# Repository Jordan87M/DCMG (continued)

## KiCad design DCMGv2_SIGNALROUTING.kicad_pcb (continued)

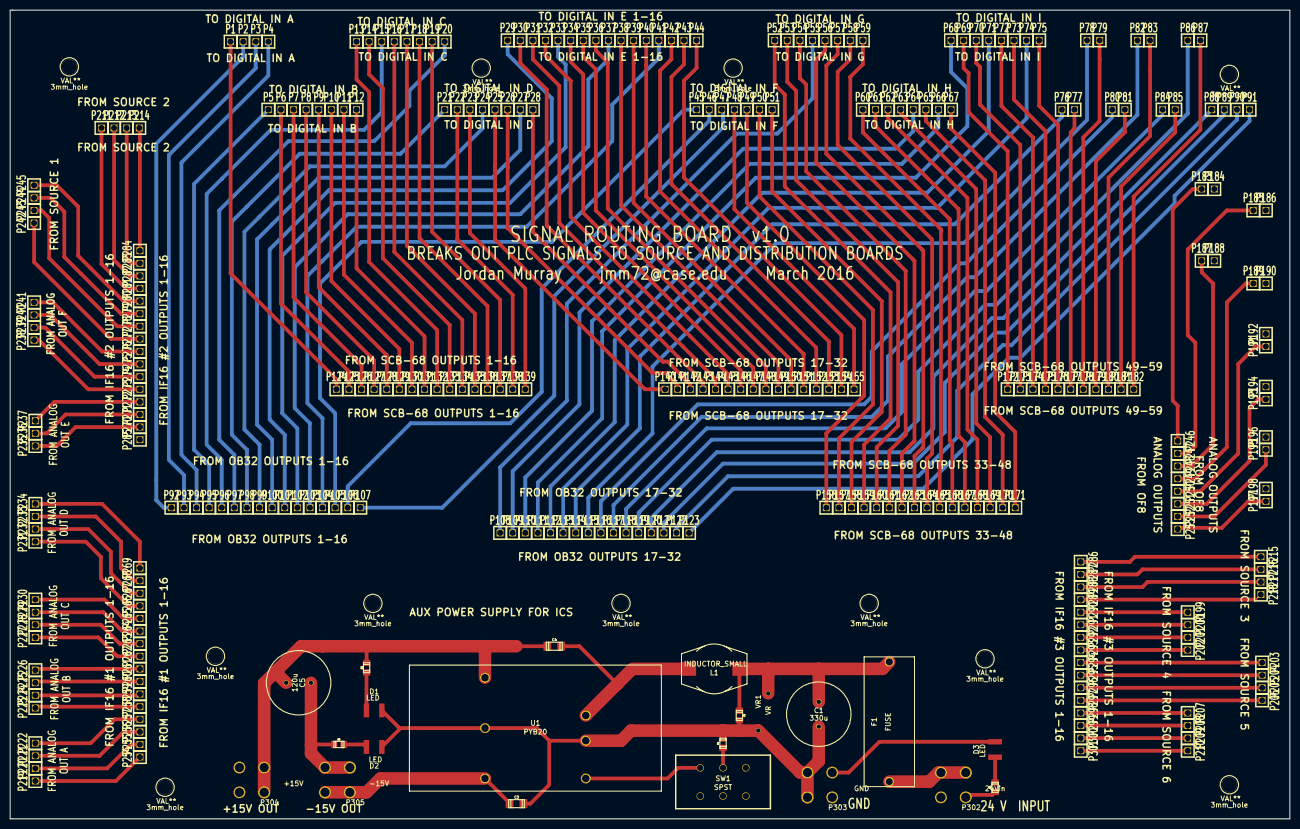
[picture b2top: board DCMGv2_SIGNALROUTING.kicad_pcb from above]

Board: 2 copper layers, 258.1 x 163.1 mm, 333 parts (0 on the bottom side), 157 nets.

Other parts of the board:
3mm_hole, 3mm_hole#2, 3mm_hole#3, 3mm_hole#4, 3mm_hole#5, 3mm_hole#6, 3mm_hole#7, 3mm_hole#8, 3mm_hole#9, 3mm_hole#10, 3mm_hole#11: VAL**; 3mm_hole

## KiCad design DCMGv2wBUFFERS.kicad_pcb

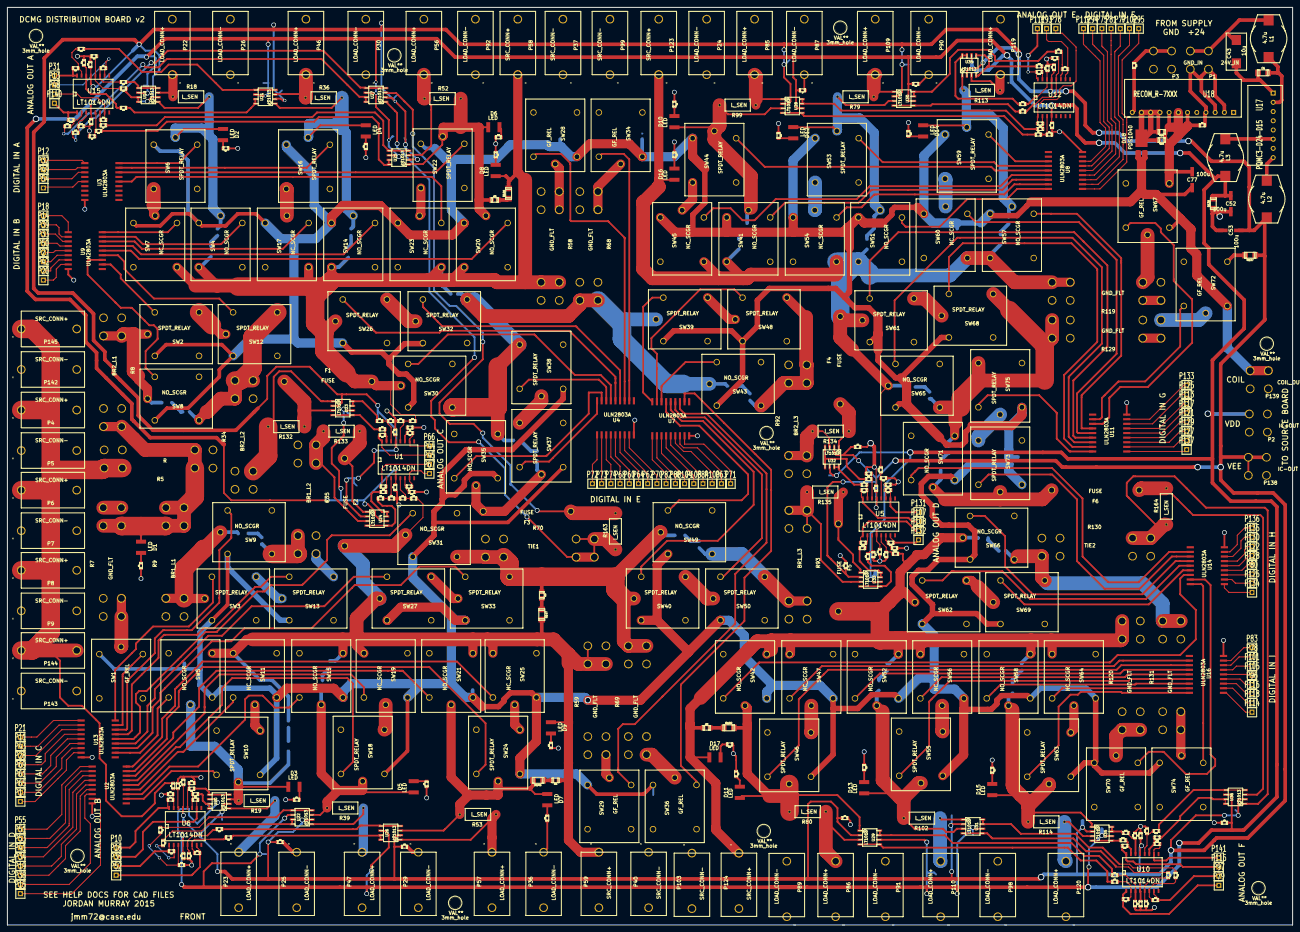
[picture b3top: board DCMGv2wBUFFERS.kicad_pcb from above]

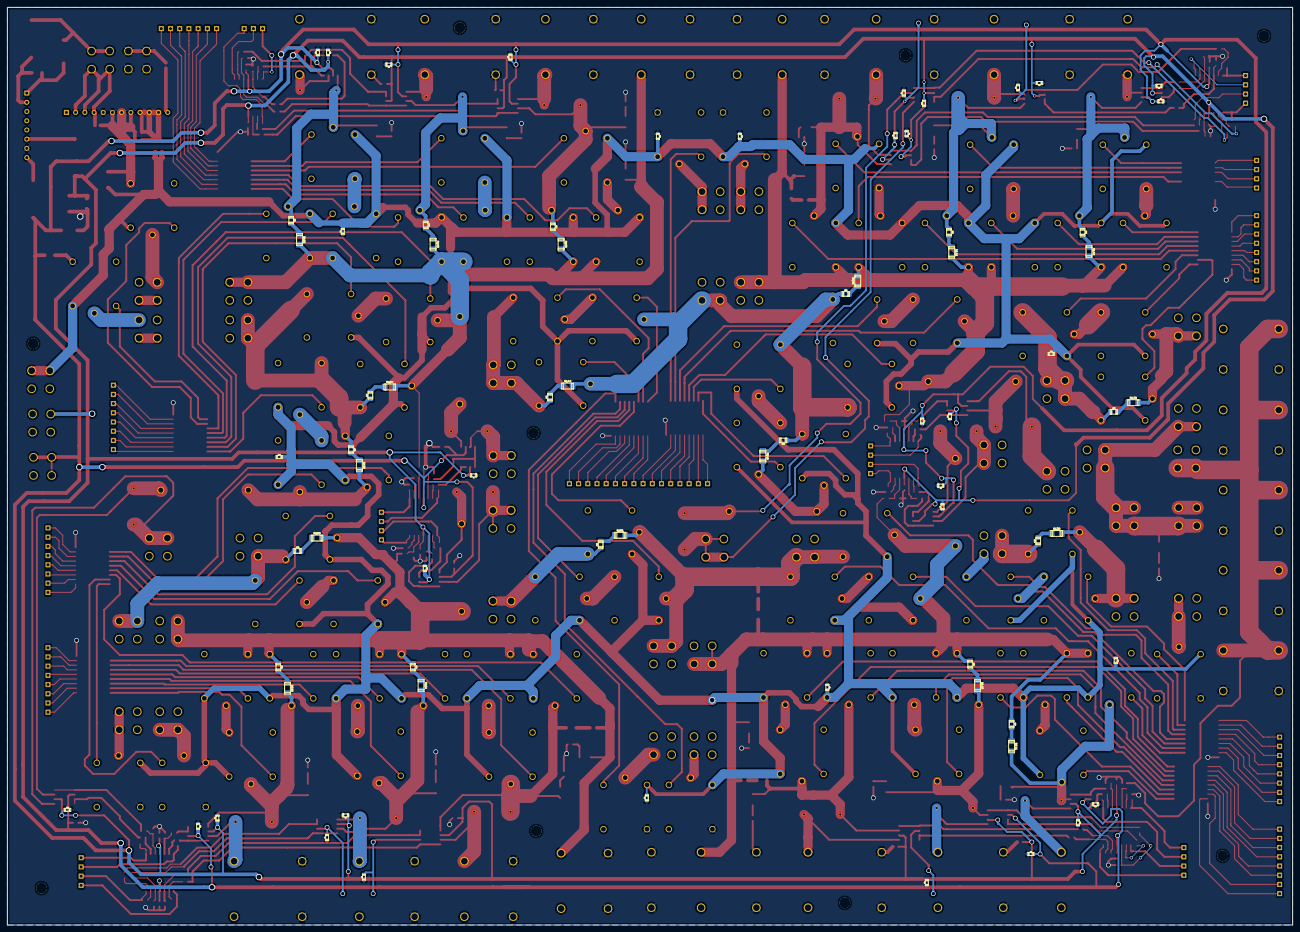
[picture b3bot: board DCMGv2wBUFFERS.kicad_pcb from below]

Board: 2 copper layers, 354.3 x 253.0 mm, 548 parts (72 on the bottom side), 389 nets.

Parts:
3mm_hole, 3mm_hole#2, 3mm_hole#3, 3mm_hole#4, 3mm_hole#5, 3mm_hole#6, 3mm_hole#7, 3mm_hole#8, 3mm_hole#9: VAL**; 3mm_hole
C1: 1u; c_1206
C2, C3, C4, C5, C6, C7, C8, C9, C10, C11, C12, C13, C14, C15, C16, C17, C18, C19, C20, C21, C22, C23, C24, C25, C26, C27, C28, C29, C30, C31, C32, C33, C34, C35, C36, C37, C38, C39, C40, C41, C42, C78, C79, C80, C81, C82, C83, C84: VCC_BYP; c_0603
C43: 10u; c_2917
C44, C45, C46, C47, C48, C49, C50, C51: COIL_BYPASS; c_0603
C52, C53, C77: 100u; PANASONIC_CAP_D8
C54, C55, C56, C57, C58, C59, C60, C61, C62, C63, C64, C65, C66, C67, C68, C69, C70, C71, C72, C73, C74, C75: C_SNUB; c_0805
C76: 1u; c_0603
D1, D2, D3, D4, D5, D6, D7, D8, D9, D10, D11, D12, D13, D14, D15, D16, D17: LED; 1209
D18: PDS1040; POWERDI5
F1, F2, F3, F4, F5, F6: FUSE; OMNI-BLOCK
L1, L2, L3: 4.7u; SDR1005
P1: 24V_IN; Screw Terminal 8191
P2: IC+OUT; Screw Terminal 8191
P3: GND_IN; Screw Terminal 8191
P4, P6, P8, P58, P59, P123, P124, P144, P145: SRC_CONN+; DELTRON BANANA
P5, P7, P9, P37, P40, P99, P103, P142, P143: SRC_CONN-; DELTRON BANANA
P10, P66, P67, P131, P132: BUS_V_SIG; SIL-1
P11, P62, P63, P70, P71, P125, P126, P133, P134: GF_SIG; SIL-1
P12, P15, P20, P21, P32, P34, P49, P51, P60, P61, P72, P75, P78, P82, P84, P94, P96, P112, P114, P121, P122, P135: CTRL_SIG; SIL-1
P13, P16, P31, P35, P44, P45, P48, P52, P76, P79, P93, P97, P107, P108, P111, P115, P140, P141: LOAD_I_SIG; SIL-1
P14, P17, P33, P38, P42, P43, P50, P53, P68, P69, P73, P77, P80, P95, P101, P104, P106, P113, P116, P129, P130, P136: NO_SCGR_SIG; SIL-1
P18, P19, P27, P28, P39, P41, P54, P55, P64, P65, P74, P81, P83, P88, P100, P102, P105, P117, P118, P127, P128, P137: NC_SCGR_SIG; SIL-1
P22, P23, P46, P47, P56, P57, P85, P86, P109, P110, P119, P120: LOAD_CONN+; DELTRON BANANA
P24, P25, P26, P29, P30, P36, P87, P89, P90, P91, P92, P98: LOAD_CONN-; DELTRON BANANA
P138: IC-OUT; Screw Terminal 8191
P139: COIL_OUT; Screw Terminal 8191
R1, R61, R63, R122, R124: VS_R2; c_0603
R2, R60, R64, R121, R125: VS_R4; c_0603
R3, R62, R65, R123, R126: VS_R1; c_0603
R4, R66, R67, R127, R128: VS_R3; c_0603
R5: R; Double Terminal 8191
R6, R20, R21, R42, R43, R54, R55, R81, R82, R103, R104, R115, R116: CLIM; c_0603
R7, R58, R59, R68, R69, R119, R120, R129, R131: GND_FLT; Double Terminal 8191
R8: BR2_L1; Double Terminal 8191
R9: BR1_L1; Double Terminal 8191
R10, R11, R22, R23, R44, R45, R71, R72, R83, R84, R105, R106, R168, R172: IS_R3; c_0603
R12, R17, R24, R31, R46, R51, R73, R78, R89, R96, R107, R112, R167, R171: IS_R1; c_0603
R13, R16, R25, R30, R47, R50, R74, R77, R90, R95, R108, R111, R166, R170: IS_R4; c_0603
R14, R15, R26, R29, R48, R49, R75, R76, R91, R94, R109, R110, R165, R169: IS_R2; c_0603
R18, R19, R36, R39, R52, R53, R79, R80, R99, R102, R113, R114: L_SEN; OHMITE_1W
R27, R28, R32, R33, R37, R38, R40, R41, R85, R86, R87, R88, R97, R98, R100, R101, R160: R; c_0603
R34: BR2_L2; Double Terminal 8191
R35: BR1_L2; Double Terminal 8191
R56, R57, R117, R118: C_LIM; c_0603
R70: TIE1; Double Terminal 8191
R92: BR2_L3; Double Terminal 8191
R93: BR1_L3; Double Terminal 8191
R130: TIE2; Double Terminal 8191
R132, R133, R134, R135, R163, R164: I_SEN; OHMITE_1W
R136, R137: MINLOAD_S; c_1206
R138, R139, R140, R141, R142, R143, R144, R145, R146, R147, R148, R149, R150, R151, R152, R153, R154, R155, R156, R157, R158, R159: R_SNUB; c_1206
R161, R162: 1k; c_0805
SW1, SW28, SW29, SW34, SW36, SW67, SW70, SW72, SW74: GF_REL; TECONN_ORWH
SW2, SW3, SW6, SW10, SW12, SW13, SW16, SW18, SW22, SW24, SW26, SW27, SW32, SW33, SW37, SW38, SW39, SW40, SW44, SW46, SW48, SW50, SW53, SW55, SW59, SW61, SW62, SW63, SW68, SW69, SW73, SW75: SPDT_RELAY; TECONN_ORWH
SW4, SW5, SW8, SW9, SW14, SW15, SW20, SW21, SW30, SW31, SW35, SW41, SW42, SW43, SW49, SW51, SW52, SW57, SW58, SW65, SW66, SW71: NO_SCGR; TECONN_ORWH
SW7, SW11, SW17, SW19, SW23, SW25, SW45, SW47, SW54, SW56, SW60, SW64: NC_SCGR; TECONN_ORWH
U1, U5, U6, U10, U12, U15: LT1014DN; SO16W
U2, U3, U4, U7, U8, U9, U11, U13, U14, U16: ULN2803A; SOIC-18
U17: PQMC3-D24-D15; SIL-8 PQMC
U18: RECOM_R-7XXX; R-7xxx_SIL-12
U19, U20, U21, U22, U23, U24, U25, U26, U27, U28, U29, U30, U31, U32, U33, U34, U35, U36: LT1013; so-8

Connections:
COIL_POW+: C44.1, C45.1, C46.1, C47.1, C48.1, C49.1, C50.1, C51.1, C77.1, D18.2, P139.1, SW1.2, SW2.2, SW3.2, SW4.2, SW5.2, SW6.2, SW7.2, SW8.2, SW9.2, SW10.2, SW11.2, SW12.2, SW13.2, SW14.2, SW15.2, SW16.2, SW17.2, SW18.2, SW19.2, SW20.2, SW21.2, SW22.2, SW23.2, SW24.2, SW25.2, SW26.2, SW27.2, SW28.2, SW29.2, SW30.2, SW31.2, SW32.2, SW33.2, SW34.2, SW35.2, SW36.2, SW37.2, SW38.2, SW39.2, SW40.2, SW41.2, SW42.2, SW43.2, SW44.2, SW45.2, SW46.2, SW47.2, SW48.2, SW49.2, SW50.2, SW51.2, SW52.2, SW53.2, SW54.2, SW55.2, SW56.2, SW57.2, SW58.2, SW59.2, SW60.2, SW61.2, SW62.2, SW63.2, SW64.2, SW65.2, SW66.2, SW67.2, SW68.2, SW69.2, SW70.2, SW71.2, SW72.2, SW73.2, SW74.2, SW75.2
GND: C1.2, C2.2, C3.2, C4.2, C5.2, C6.2, C7.2, C8.2, C9.2, C10.1, C11.1, C12.1, C13.1, C14.1, C15.1, C16.2, C17.1, C18.1, C19.1, C20.2, C21.1, C22.1, C23.2, C24.2, C25.2, C26.2, C27.2, C28.2, C29.2, C30.2, C31.1, C32.1, C33.1, C34.1, C35.1, C36.1, C37.1, C38.1, C39.2, C40.1, C41.2, C42.1, C43.2, C44.2, C45.2, C46.2, C47.2, C48.2, C49.2, C50.2, C51.2, C52.2, C53.1, C76.2, C77.2, C78.2, C79.1, C80.2, C81.1, C82.2, C83.2, C84.1, P3.1, P5.1, P7.1, P9.1, P24.1, P25.1, P26.1, P29.1, P30.1, P36.1, P37.1, P40.1, P87.1, P89.1, P90.1, P91.1, P92.1, P98.1, P99.1, P103.1, P142.1, P143.1, R2.2, R3.2, R6.2, R13.1, R16.1, R20.2, R21.2, R25.1, R30.1, R32.1, R33.1, R42.2, R43.2, R47.1, R50.1, R54.2, R55.2, R56.2, R57.2, R60.2, R62.2, R64.2, R65.2, R74.1, R77.1, R81.2, R82.2, R87.1, R88.1, R90.1, R95.1, R103.2, R104.2, R108.1, R111.1, R115.2, R116.2, R117.2, R118.2, R121.2, R123.2, R125.2, R126.2, R136.2, R137.1, R160.2, R161.2, R162.2, R166.1, R170.1, SW1.10, SW28.10, SW29.10, SW34.10, SW36.10, SW67.10, SW70.10, SW72.10, SW74.10, U2.9, U3.9, U4.9, U7.9, U8.9, U9.9, U11.9, U13.9, U14.9, U16.9, U17.1, U17.7, U18.5, U18.6, U18.7, U18.8
IC_POW+: C2.1, C3.1, C4.1, C5.1, C6.1, C7.1, C8.1, C9.1, C16.1, C20.1, C23.1, C24.1, C25.1, C26.1, C27.1, C28.1, C29.1, C30.1, C39.1, C41.1, C52.1, C78.1, C80.1, C82.1, C83.1, L3.2, P2.1, R136.1, U1.4, U5.4, U6.4, U10.4, U12.4, U15.4, U19.6, U20.6, U21.6, U22.6, U23.6, U24.6, U25.6, U26.6, U27.6, U28.6, U29.6, U30.6, U31.6, U32.6, U33.6, U34.6, U35.6, U36.6
IC_POW-: C10.2, C11.2, C12.2, C13.2, C14.2, C15.2, C17.2, C18.2, C19.2, C21.2, C22.2, C31.2, C32.2, C33.2, C34.2, C35.2, C36.2, C37.2, C38.2, C40.2, C42.2, C53.2, C79.2, C81.2, C84.2, L2.2, P138.1, R137.2, U1.13, U5.13, U6.13, U10.13, U12.13, U15.13, U19.2, U20.2, U21.2, U22.2, U23.2, U24.2, U25.2, U26.2, U27.2, U28.2, U29.2, U30.2, U31.2, U32.2, U33.2, U34.2, U35.2, U36.2
unnamed: P56.1, R52.2, U25.3
unnamed: P46.1, R36.2, U21.3
unnamed: P48.1, R44.1, U15.7
unnamed: SW60.9, U11.14
unnamed: SW57.9, U11.13
unnamed: P117.1, U11.5
unnamed: SW59.9, U8.12
unnamed: SW59.10, SW60.5
unnamed: R44.2, R46.1, U15.6
unnamed: P113.1, U11.6
unnamed: P112.1, U8.7
unnamed: P125.1, U11.7
unnamed: P66.1, R66.2, U1.10
unnamed: R13.2, R14.1, U15.12
unnamed: P22.1, R18.2, U19.3
unnamed: SW6.10, SW7.5
unnamed: R62.1, R66.1, U1.11
unnamed: R47.2, R48.1, U15.5
unnamed: P31.1, R22.1, U15.16
unnamed: R22.2, R24.1, U15.15
unnamed: R25.2, R26.1, U15.14
unnamed: P13.1, R10.1, U15.10
unnamed: R10.2, R12.1, U15.11
unnamed: R121.1, R122.2, U5.12
unnamed: R123.1, R127.1, U5.11
unnamed: P131.1, R127.2, U5.10
unnamed: SW44.10, SW45.5
unnamed: R119.2, SW67.5
unnamed: D10.2, R81.1
unnamed: D12.2, R103.1
unnamed: D14.2, R115.1
unnamed: P76.1, R71.1, U12.1
unnamed: R71.2, R73.1, U12.2
unnamed: R74.2, R75.1, U12.3
unnamed: SW53.9, U8.13
unnamed: SW53.10, SW54.5
unnamed: SW54.9, U8.17
unnamed: P102.1, U8.2
unnamed: SW51.9, U8.18
unnamed: P95.1, U8.1
unnamed: P94.1, U8.6
unnamed: D16.2, R117.1
unnamed: SW44.9, U8.14
unnamed: SW67.9, U11.12
unnamed: SW45.9, U8.15
unnamed: P81.1, U8.4
unnamed: SW41.9, U8.16
unnamed: P77.1, U8.3
unnamed: P75.1, U8.5
unnamed: P79.1, R72.1, U10.1
unnamed: R94.1, R95.2, U10.5
unnamed: R84.2, R96.1, U10.6
unnamed: P97.1, R84.1, U10.7
unnamed: R72.2, R78.1, U10.2
unnamed: P86.1, R80.2, U29.3
unnamed: R76.1, R77.2, U10.3
unnamed: P110.1, R102.2, U31.1
unnamed: P120.1, R114.2, U35.3
unnamed: P115.1, R106.1, U10.16
unnamed: R106.2, R112.1, U10.15
unnamed: R110.1, R111.2, U10.14
unnamed: D17.2, R118.1
unnamed: D15.2, R116.1
unnamed: D13.2, R104.1
unnamed: D11.2, R82.1
unnamed: SW46.9, U16.12
unnamed: SW70.9, U14.17
unnamed: SW47.9, U16.11
unnamed: P132.1, R128.2, U5.7
unnamed: D11.1, R80.1, R152.1, SW42.5, SW46.5, U29.1
unnamed: SW46.10, SW47.5
unnamed: R126.1, R128.1, U5.6
unnamed: R124.2, R125.1, U5.5
unnamed: R120.2, SW70.5
unnamed: SW28.9, U4.12
unnamed: SW6.9, U3.18
unnamed: P14.1, U9.2
unnamed: SW4.9, U9.17
unnamed: P18.1, U9.1
unnamed: SW7.9, U9.18
unnamed: P12.1, U3.1
unnamed: SW16.10, SW17.5
unnamed: D4.2, R42.1
unnamed: R60.1, R61.2, U1.12
unnamed: R58.2, SW28.5
unnamed: D2.2, R20.1
unnamed: D6.2, R54.1
unnamed: D8.2, R56.1
unnamed: P50.1, U9.5
unnamed: P62.1, U4.7
unnamed: P49.1, U3.3
unnamed: SW22.9, U3.16
unnamed: SW20.9, U9.14
unnamed: P54.1, U3.5
unnamed: SW23.9, U3.14
unnamed: SW16.9, U3.17
unnamed: SW17.9, U9.16
unnamed: P39.1, U9.3
unnamed: SW14.9, U9.15
unnamed: P33.1, U9.4
unnamed: P32.1, U3.2
unnamed: R90.2, R91.1, U12.12
unnamed: SW22.10, SW23.5
unnamed: R169.1, R170.2, U10.12
unnamed: R171.1, R172.2, U10.11
unnamed: P141.1, R172.1, U10.10
unnamed: C63.2, R69.1, R70.2, R151.1, SW31.10, SW33.1, SW40.5, SW49.5
unnamed: F3.1, R163.1, U27.3
unnamed: R70.1, R163.2, U27.1
unnamed: D3.1, R19.1, R141.1, SW5.5, SW10.5, U20.3
unnamed: R15.2, U20.4, U20.5
unnamed: P140.1, R168.1, U15.1
unnamed: R167.1, R168.2, U15.2
unnamed: R165.1, R166.2, U15.3
unnamed: R9.2, R138.1, SW3.5, SW9.5
unnamed: R160.1, U18.12
unnamed: D18.1, R161.1, R162.1, U18.9, U18.10, U18.11
unnamed: R46.2, U25.4, U25.5
unnamed: R48.2, U25.7, U25.8
unnamed: R165.2, U27.4, U27.5
unnamed: R112.2, U35.4, U35.5
unnamed: R110.2, U35.7, U35.8
unnamed: R12.2, U19.4, U19.5
unnamed: R26.2, U21.7, U21.8
unnamed: R24.2, U21.4, U21.5
unnamed: R167.2, U27.7, U27.8
unnamed: R49.2, U26.4, U26.5
unnamed: R31.2, U22.7, U22.8
unnamed: D7.1, R53.1, R145.1, SW21.5, SW24.5, U26.3
unnamed: P47.1, R39.2, U22.1
unnamed: P57.1, R53.2, U26.1
unnamed: R29.2, U22.4, U22.5
unnamed: D5.1, R39.1, R143.1, SW15.5, SW18.5, U22.3
unnamed: R17.2, U20.7, U20.8
unnamed: P23.1, R19.2, U20.1
unnamed: R78.2, U29.4, U29.5
unnamed: R96.2, U31.7, U31.8
unnamed: R94.2, U31.4, U31.5
unnamed: L3.1, U17.6
unnamed: R76.2, U29.7, U29.8
unnamed: R51.2, U26.7, U26.8
unnamed: C56.1, R139.2
unnamed: C62.1, R146.2
unnamed: C65.1, R149.2
unnamed: C73.1, R157.2
unnamed: C74.1, R158.2
unnamed: C59.1, R143.2
unnamed: C58.1, R142.2
unnamed: C72.1, R156.2
unnamed: C70.1, R154.2
unnamed: C67.1, R152.2
unnamed: C61.1, R145.2
unnamed: C57.1, R141.2
unnamed: C55.2, D2.1, R18.1, SW4.5, SW6.5, U19.1
unnamed: C55.1, R140.2
unnamed: C54.1, R138.2
unnamed: C63.1, R147.2
unnamed: C68.1, R151.2
unnamed: R105.2, R107.1, U12.15
unnamed: P111.1, R105.1, U12.16
unnamed: R108.2, R109.1, U12.14
unnamed: P93.1, R83.1, U12.10
unnamed: R83.2, R89.1, U12.11
unnamed: C58.2, D4.1, R36.1, SW14.5, SW16.5, U21.1
unnamed: C60.2, D6.1, R52.1, SW20.5, SW22.5, U25.1
unnamed: C74.2, R130.2, R131.1, SW66.10, SW69.1
unnamed: C68.2, R93.1, SW49.10, SW50.1
unnamed: L2.1, U17.8
unnamed: C43.1, C76.1, L1.1, P1.1, U18.2, U18.3, U18.4
unnamed: C1.1, L1.2, U17.2
unnamed: C71.1, R155.2
unnamed: C69.1, R153.2
unnamed: C66.1, R150.2
unnamed: C60.1, R144.2
unnamed: C64.1, R148.2
unnamed: C75.1, R159.2
unnamed: F6.2, R159.1, SW71.5, SW73.5
unnamed: P83.1, U16.8
unnamed: P17.1, U13.8
unnamed: SW5.9, U13.11
unnamed: P19.1, U2.6
unnamed: SW11.9, U2.13
unnamed: SW10.9, U2.11
unnamed: SW2.1, SW12.5
unnamed: SW3.1, SW13.5
unnamed: SW29.9, U7.12
unnamed: P15.1, U2.8
unnamed: SW18.10, SW19.5
unnamed: SW3.9, U13.18
unnamed: SW13.9, U13.15
unnamed: R1.2, R2.1, U6.14
unnamed: R8.2, R139.1, SW2.5, SW8.5
unnamed: C56.2, R34.1, SW8.10, SW12.1
unnamed: SW12.9, U9.13
unnamed: SW2.9, U9.11
unnamed: SW8.9, U9.12
unnamed: SW21.9, U2.16
unnamed: P63.1, U7.7
unnamed: P51.1, U2.2
unnamed: SW24.9, U2.17
unnamed: P53.1, U2.3
unnamed: P55.1, U2.1
unnamed: SW25.9, U2.18
unnamed: P28.1, U13.4
unnamed: P21.1, U13.1
unnamed: SW9.9, U13.16
unnamed: P43.1, U13.3
unnamed: SW18.9, U2.14
unnamed: SW19.9, U2.15
unnamed: P41.1, U2.4
unnamed: SW15.9, U2.12
unnamed: P38.1, U2.7
unnamed: P34.1, U2.5
unnamed: SW24.10, SW25.5
unnamed: R59.2, SW29.5
unnamed: C54.2, R35.1, SW9.10, SW13.1
unnamed: D3.2, R21.1
unnamed: D5.2, R43.1
unnamed: D7.2, R55.1
unnamed: D9.2, R57.1
unnamed: P67.1, R67.2, U1.7
unnamed: SW10.10, SW11.5
unnamed: R65.1, R67.1, U1.6
unnamed: R63.2, R64.1, U1.5
unnamed: P10.1, R4.2, U6.16
unnamed: R3.1, R4.1, U6.15
unnamed: D1.2, R6.1
unnamed: D1.1, R5.2, R7.1, R8.1, R9.1
unnamed: P4.1, P6.1, P8.1, P144.1, P145.1, R1.1, R5.1
unnamed: R37.2, U23.4, U23.5
unnamed: F1.1, R132.2, U23.3
unnamed: R34.2, R132.1, U23.1
unnamed: R27.2, U23.7, U23.8
unnamed: R92.2, R134.1, U32.3
unnamed: R35.2, R133.1, U24.3
unnamed: F2.1, R133.2, U24.1
unnamed: R38.2, U24.7, U24.8
unnamed: R28.2, U24.4, U24.5
unnamed: R98.2, U33.7, U33.8
unnamed: R93.2, R135.1, U33.3
unnamed: R86.2, U33.4, U33.5
unnamed: F5.1, R135.2, U33.1
unnamed: F4.1, R134.2, U32.1
unnamed: R97.2, U32.7, U32.8
unnamed: R85.2, U32.4, U32.5
unnamed: SW66.9, U14.13
unnamed: SW61.1, SW68.5
unnamed: SW69.9, U14.15
unnamed: SW65.9, U11.16
unnamed: SW61.9, U11.15
unnamed: SW68.9, U11.17
unnamed: D16.1, F4.2, P123.1, R119.1, R122.1, R150.1, R153.1, R155.1, R157.1, SW41.10, SW45.1, SW51.10, SW54.1, SW57.10, SW60.1, SW61.5, SW65.5
unnamed: SW62.9, U14.14
unnamed: P128.1, U14.4
unnamed: P122.1, U14.5
unnamed: P130.1, U14.6
unnamed: SW73.1, SW75.5
unnamed: SW71.9, U14.11
unnamed: SW73.9, U14.12
unnamed: SW75.9, U11.18
unnamed: P127.1, U11.2
unnamed: P121.1, U11.4
unnamed: P129.1, U11.3
unnamed: SW43.9, U7.16
unnamed: P104.1, U7.3
unnamed: P82.1, U7.1
unnamed: P88.1, U7.2
unnamed: SW39.9, U7.18
unnamed: SW48.9, U7.17
unnamed: C65.2, R92.1, SW43.10, SW48.1
unnamed: SW40.1, SW50.5
unnamed: SW49.9, U7.15
unnamed: SW40.9, U7.14
unnamed: P106.1, U7.4
unnamed: SW62.1, SW69.5
unnamed: SW50.9, U7.13
unnamed: P100.1, U7.6
unnamed: P84.1, U7.5
unnamed: D15.1, R114.1, R156.1, SW58.5, SW63.5, U35.1
unnamed: SW63.10, SW64.5
unnamed: P96.1, U16.4
unnamed: SW55.9, U16.15
unnamed: P101.1, U16.6
unnamed: SW63.9, U16.18
unnamed: SW64.9, U16.17
unnamed: P118.1, U16.2
unnamed: SW58.9, U16.16
unnamed: P116.1, U16.3
unnamed: D13.1, R102.1, R154.1, SW52.5, SW55.5, U31.3
unnamed: SW42.9, U14.16
unnamed: P80.1, U14.3
unnamed: P78.1, U16.7
unnamed: P114.1, U16.1
unnamed: C67.2, C70.2, C72.2, D17.1, F5.2, P124.1, R120.1, R124.1, R158.1, SW42.10, SW47.1, SW52.10, SW56.1, SW58.10, SW62.5, SW64.1, SW66.5
unnamed: SW55.10, SW56.5
unnamed: SW56.9, U16.14
unnamed: P105.1, U16.5
unnamed: SW52.9, U16.13
unnamed: C73.2, C75.2, R129.1, SW65.10, SW68.1, SW71.10, SW75.1
unnamed: P71.1, U7.8
unnamed: SW36.9, U7.11
unnamed: R69.2, SW36.5
unnamed: P137.1, U11.1
unnamed: P135.1, U14.7
unnamed: P136.1, U14.8
unnamed: P126.1, U14.2
unnamed: R68.2, SW34.5
unnamed: SW34.9, U4.11
unnamed: P70.1, U4.8
unnamed: R129.2, SW72.5
unnamed: SW72.9, U11.11
unnamed: P133.1, U11.8
unnamed: R131.2, SW74.5
unnamed: SW74.9, U14.18
unnamed: P134.1, U14.1
unnamed: R7.2, SW1.5
unnamed: SW1.9, U13.17
unnamed: P11.1, U13.2
unnamed: R38.1, R41.2, U1.2
unnamed: P45.1, R41.1, U1.1
unnamed: R86.1, R88.2, U5.3
unnamed: R28.1, R33.2, U1.3
unnamed: R85.1, R87.2, U5.14
unnamed: P44.1, R40.1, U1.16
unnamed: R37.1, R40.2, U1.15
unnamed: R27.1, R32.2, U1.14
unnamed: P108.1, R101.1, U5.1
unnamed: R98.1, R101.2, U5.2
unnamed: P16.1, R11.1, U6.10
unnamed: R29.1, R30.2, U6.3
unnamed: R23.2, R31.1, U6.2
unnamed: P35.1, R23.1, U6.1
unnamed: R11.2, R17.1, U6.11
unnamed: R15.1, R16.2, U6.12
unnamed: P52.1, R45.1, U6.7
unnamed: R45.2, R51.1, U6.6
unnamed: R49.1, R50.2, U6.5
unnamed: P69.1, U13.5
unnamed: P61.1, U13.6
unnamed: P65.1, U13.7
unnamed: SW27.9, U13.13
unnamed: SW33.9, U13.12
unnamed: SW31.9, U13.14
unnamed: SW37.1, SW38.5
unnamed: C57.2, C59.2, C61.2, D9.1, F2.2, P59.1, R59.1, R63.1, R147.1, SW5.10, SW11.1, SW15.10, SW19.1, SW21.10, SW25.1, SW27.5, SW31.5
unnamed: SW39.1, SW48.5
unnamed: SW35.9, U4.17
unnamed: SW38.9, U4.16
unnamed: SW37.9, U4.18
unnamed: P74.1, U4.3
unnamed: P72.1, U4.1
unnamed: P73.1, U4.2
unnamed: F3.2, R148.1, SW35.5, SW37.5
unnamed: P42.1, U9.7
unnamed: P20.1, U9.8
unnamed: P27.1, U9.6
unnamed: SW26.1, SW32.5
unnamed: P107.1, R100.1, U5.16
unnamed: R97.1, R100.2, U5.15
unnamed: SW27.1, SW33.5
unnamed: SW30.9, U4.15
unnamed: C62.2, C64.2, R68.1, R149.1, SW30.10, SW32.1, SW35.10, SW38.1, SW39.5, SW43.5
unnamed: SW32.9, U4.13
unnamed: SW26.9, U4.14
unnamed: P64.1, U4.6
unnamed: P60.1, U4.5
unnamed: P68.1, U4.4
unnamed: D8.1, F1.2, P58.1, R58.1, R61.1, R140.1, R142.1, R144.1, R146.1, SW4.10, SW7.1, SW14.10, SW17.1, SW20.10, SW23.1, SW26.5, SW30.5
unnamed: C69.2, D12.1, R79.1, SW51.5, SW53.5, U30.3
unnamed: P85.1, R99.2, U28.1
unnamed: R91.2, U30.4, U30.5
unnamed: R89.2, U30.7, U30.8
unnamed: P109.1, R79.2, U30.1
unnamed: C66.2, D10.1, R99.1, SW41.5, SW44.5, U28.3
unnamed: F6.1, R164.1, U36.3
unnamed: P119.1, R113.2, U34.3
unnamed: C71.2, D14.1, R113.1, SW57.5, SW59.5, U34.1
unnamed: R109.2, U34.7, U34.8
unnamed: R107.2, U34.4, U34.5
unnamed: R14.2, U19.7, U19.8
unnamed: R130.1, R164.2, U36.1
unnamed: R171.2, U36.7, U36.8
unnamed: R169.2, U36.4, U36.5
unnamed: R75.2, U28.4, U28.5
unnamed: R73.2, U28.7, U28.8

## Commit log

2016-02-14 first git version. taken from 01162015 version. current focus on distribution board
2016-02-15 thicker traces and vias. some vias still drilled incorrectly
2016-02-16 split source board into single channel test board and multi channel board with power supply. All vias have been fixed. NOTE: in the first logged comment, I meant to say that I was working on the SOUR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
2016-03-03 added power indicators. added mounting holes. board size increased slightly in y dim. fixed important schematic and routing error involving U8B and U8D!
2016-03-03 snubber capacitors now 0805
2016-03-11 added labels and made IC power traces thicker
2016-03-11 generated fabrication files
2016-03-11 shortened board in X direction and remade fab files
2016-03-22 Thicker traces and added mounting holes. Larger spaces between traces.
2016-03-22 most traces are triple thickness
2016-03-23 all traces triple thickness. improved routing
2016-03-24 put power circuit on routing board
2016-03-24 improved silk screen labels and reduced board size
2016-03-24 generated fab files
2016-03-25 moved a few traces a little bit. fab files now include solder masks
2016-03-31 replaced SPST slider footprint. More importantly, I fixed the following issues from the prototype test source board: 1. over current protection transistor drain and source were reversed. 2. U12 negat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
2016-04-03 reduce need for output voltage protection by switching output current sensing to low side. made associated changes in output voltage measurement (Vout+ to Vout- is now distinct from Vout+ to gnd)
2016-04-09 added optional filtering capacitors for measurement amplifiers. corrected zener clamps to clamp high AND low voltages.
2016-04-12 separated transistors for heat sink clearance
